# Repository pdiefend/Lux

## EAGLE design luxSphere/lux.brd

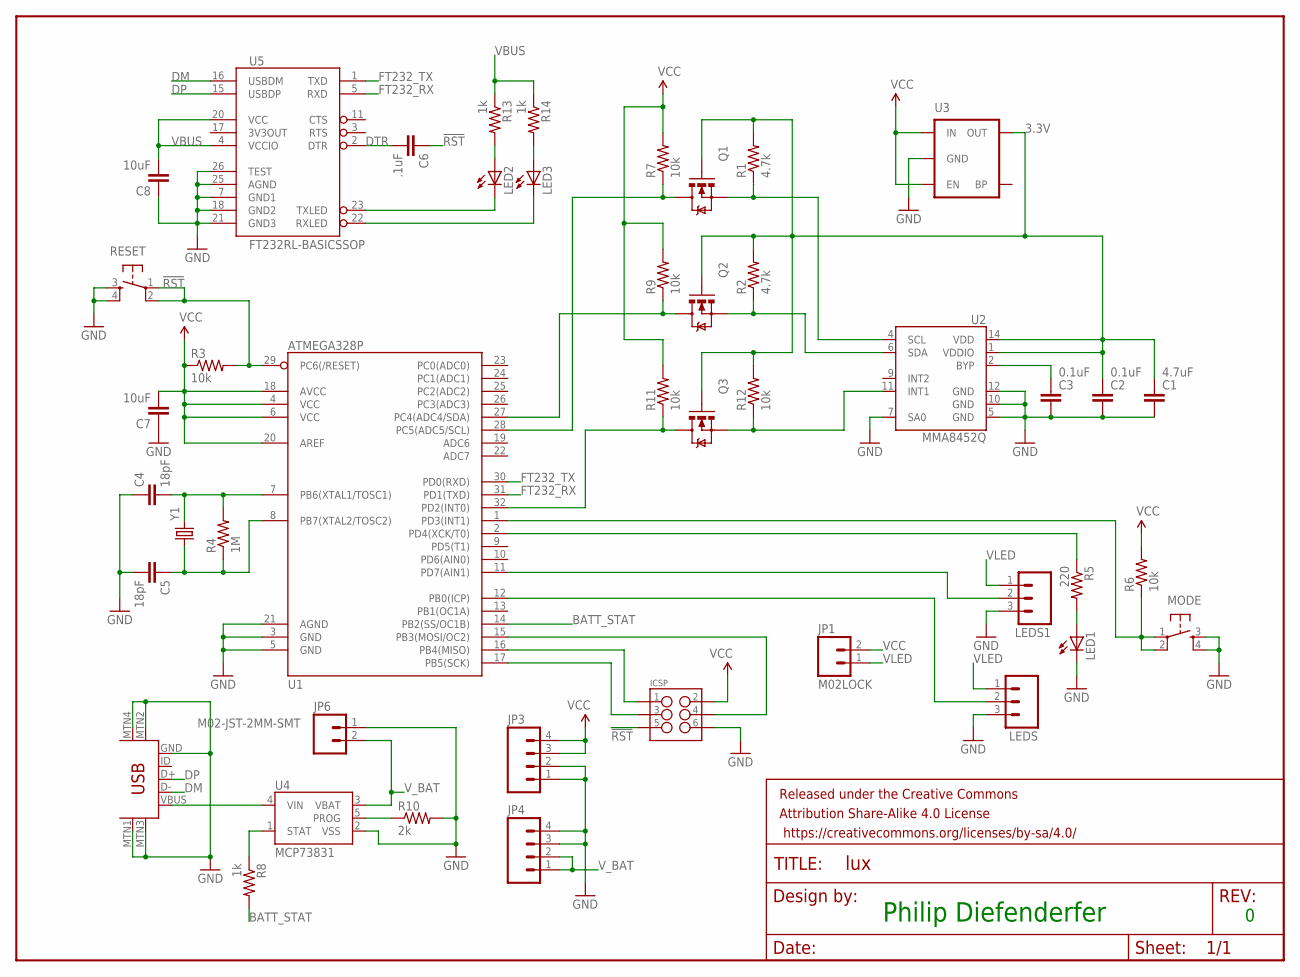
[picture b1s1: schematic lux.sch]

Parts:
C1: 4.7uF; 0603-CAP
C2, C3: 0.1uF; 0603-CAP
C4, C5: 18pF; 0603-CAP
C6: .1uF; 0603-CAP
C7, C8: 10uF; 0603-CAP
FRAME1: FRAME-LETTER; CREATIVE_COMMONS
ICSP: M03X2POGO_PINS; 2X3_POGO
JP1: M02LOCK; 1X02_LOCK
JP3, JP4: M04LOCK; 1X04_LOCK
JP6: M02-JST-2MM-SMT; JST-2-SMD
JP7: USB-MINIB-5PIN; USB-MINIB
LED1, LED2, LED3: LED0603; LED-0603
LEDS, LEDS1: M03PTH; 1X03
MODE: TAC_SWITCHSMD; TACTILE_SWITCH_SMD
Q1, Q2, Q3: MOSFET-NCHANNELBSS138; SOT23
R1, R2: 4.7k; 0603-RES
R3, R6, R7, R9, R11, R12: 10k; 0603-RES
R4: 1M; 0603-RES
R5: 220; 0603-RES
R8, R13, R14: 1k; 0603-RES
R10: 2k; 0603-RES
RESET: TAC_SWITCHSMD; TACTILE_SWITCH_SMD
U1: ATMEGA328P; TQFP32-08
U2: MMA8452Q; QFN-16_0.5MM
U3: MIC52053.3V; SOT23-5
U4: MCP73831; SOT23-5
U5: FT232RL-BASICSSOP; SSOP28DB
Y1: CRYSTAL5X3; CRYSTAL-SMD-5X3

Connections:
3.3V: C1.1, C2.1, Q1.1 (G), Q2.1 (G), Q3.1 (G), R1.2, R2.2, R12.2, U2.1 (VDDIO), U2.14 (VDD), U3.5 (OUT)
!RST: C6.1, ICSP.P$5 (5), R3.2, RESET.1, RESET.2, U1.29 (PC6(/RESET))
BATT_STAT: R8.2, U1.14 (PB2(SS/OC1B))
DM: JP7.D-, U5.16 (USBDM)
DP: JP7.D+, U5.15 (USBDP)
DTR: C6.2, U5.2 (DTR)
FT232_RX: U1.31 (PD1(TXD)), U5.5 (RXD)
FT232_TX: U1.30 (PD0(RXD)), U5.1 (TXD)
GND: C1.2, C2.2, C3.2, C4.1, C5.2, C7.1, C8.1, ICSP.P$6 (6), JP3.1, JP3.2, JP4.3, JP4.4, JP6.1 (2), JP7.GND, JP7.MTN1 (MTN2), JP7.MTN2 (MTN3), JP7.MTN3 (MTN1), JP7.MTN4, LED1.C, LEDS.3, LEDS1.3, MODE.3, MODE.4, R10.2, RESET.3, RESET.4, U1.3 (GND), U1.5 (GND), U1.21 (AGND), U2.5 (GND), U2.7 (SA0), U2.10 (GND), U2.12 (GND), U3.2 (GND), U4.2 (VSS), U5.7 (GND1), U5.18 (GND2), U5.21 (GND3), U5.25 (AGND), U5.26 (TEST)
N: R8.1, U4.1 (STAT)
unnamed: R10.1, U4.5 (PROG)
unnamed: LED2.C, U5.23 (TXLED)
unnamed: C3.1, U2.2 (BYP)
unnamed: ICSP.P$1 (1), U1.16 (PB4(MISO))
unnamed: LED1.A, R5.2
unnamed: ICSP.P$3 (3), U1.17 (PB5(SCK))
unnamed: MODE.1, MODE.2, R6.1, U1.1 (PD3(INT1))
unnamed: ICSP.P$4 (4), U1.15 (PB3(MOSI/OC2))
unnamed: C4.2, R4.2, U1.7 (PB6(XTAL1/TOSC1)), Y1.3 (2)
unnamed: C5.1, R4.1, U1.8 (PB7(XTAL2/TOSC2)), Y1.1
unnamed: R5.1, U1.2 (PD4(XCK/T0))
unnamed: LED3.C, U5.22 (RXLED)
unnamed: LED2.A, R13.2
unnamed: Q3.2 (S), R12.1, U2.11 (INT1)
unnamed: LED3.A, R14.2
unnamed: Q1.2 (S), R1.1, U2.4 (SCL)
unnamed: Q1.3 (D), R7.1, U1.28 (PC5(ADC5/SCL))
unnamed: Q2.2 (S), R2.1, U2.6 (SDA)
unnamed: Q2.3 (D), R9.1, U1.27 (PC4(ADC4/SDA))
unnamed: Q3.3 (D), R11.1, U1.32 (PD2(INT0))
P7: LEDS1.2, U1.11 (PD7(AIN1))
P8: LEDS.2, U1.12 (PB0(ICP))
VBUS: C8.2, JP7.VBUS, R13.1, R14.1, U4.4 (VIN), U5.4 (VCCIO), U5.20 (VCC)
VCC: C7.2, ICSP.P$2 (2), JP1.2, JP3.3, JP3.4, R3.1, R6.2, R7.2, R9.2, R11.2, U1.4 (VCC), U1.6 (VCC), U1.18 (AVCC), U1.20 (AREF), U3.1 (IN), U3.3 (EN)
VLED: JP1.1, LEDS.1, LEDS1.1
V_BAT: JP4.1, JP4.2, JP6.2 (1), U4.3 (VBAT)

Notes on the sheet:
Philip Diefenderfer

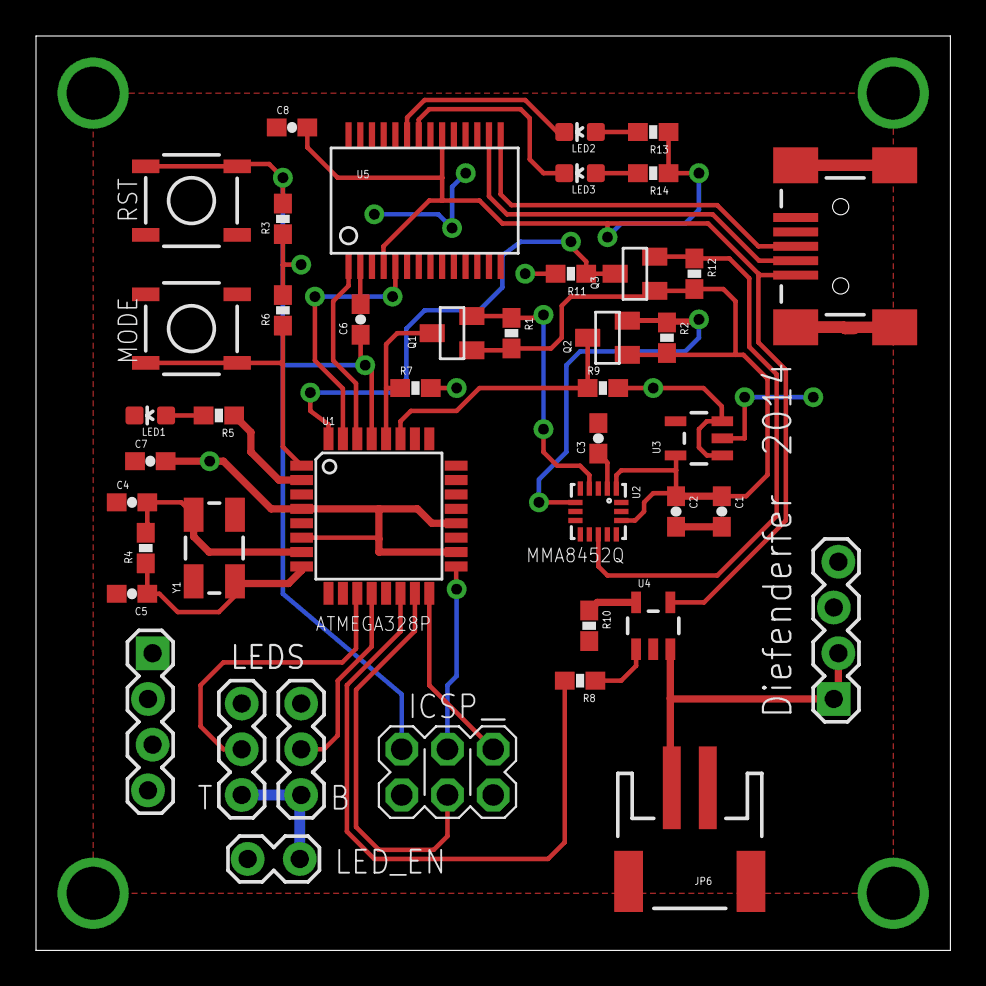
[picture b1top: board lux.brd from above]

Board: 2 copper layers, 50.8 x 50.8 mm, 45 parts (0 on the bottom side), 36 nets.

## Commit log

2016-04-09 Adding gitignore
2016-04-09 Pushing existing hardware design files to github. These will not change unless I build a new version of Lux (which I may or may not be working on)
2016-04-09 Pushing existing code before the repo was created.
2016-04-10 Broke lux.ino into different files in preparation of merging all the various modes scattered across the sketches into one main file. Also added a Game of Life sketch in preparation of a new mode.

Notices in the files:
parts and their libraries:
SparkFun-DigitalIC: Licensing: CC v3.0 Share-Alike You are welcome to use this library for commercial purposes.
SparkFun-LED: Licensing: Creative Commons ShareAlike 4.0 International - https://creativecommons.org/licenses/by-sa/4.0
SparkFun-Aesthetics: https://creativecommons.org/licenses/by-sa/4.0
